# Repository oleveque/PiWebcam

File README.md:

# PiWebcam
* Rémi Armand, *remi.armand@ens-paris-saclay.fr*
* Olivier Lévêque, *olivier.leveque@ens-paris-saclay.fr*

Ce projet, proposé en M2 FeSUP GE à l'École Normale Supérieure Paris-Saclay, a pour objectif de réaliser un système permettant de commander l’orientation d’une webcam à partir d’un serveur web embarqué. Il se base sur l'utilisation d'une *Raspberry Pi 3* et d'un microcontrôleur *AVR-T32U4* (similaire à une *Arduino Leonardo*).

Ce système, nommé *PiWebcam*, vous est présenté en image ci-dessous.

Nous décrirons dans ce manuel son fonctionnement et nous détaillerons son installation et sa configuration.

La chronologie adoptée sera la suivante :
1. Description globale du système ;
2. Configuration du microcontrôleur *AVR-T32U4* ;
3. Installation et configuration de l'ensemble du système Linux sur *Raspberry Pi 3*.

## Description globale du système
Le système PiWebcam répond à la problématique suivante.
> Piloter une webcam à distance en commandant son orientation et son zoom à l’aide d’un serveur embarqué.

La partie matériel, nommé *Cardan 3 axes* et permettant l'orientation de la caméra, est issue d'un projet ultérieur. Seul l'étage d'alimentation a été révisé et une *Raspberry Pi 3* + *PiCamera v2.1* ajoutées. Le diagramme de définition de bloc suivant permet de décomposer le système *PiWebcam* en différents sous-systèmes que nous décrirons dans ce document.

### Cardan 3 axes
Ce sous-système est composé de 2 servomoteurs ([*HS-5565MH*](Ressources/Datasheets/hs5565.pdf)) commandés en position assurant la rotation de la caméra autour de l'axe de roulis et l'axe de tangage, et d'un servomoteur ([*HS-805BB*](Ressources/Datasheets/hs805.pdf)) modifié assurant la rotation de la caméra autour de l'axe de lacet. Ce dernier est commandé en vitesse et permet une rotation totale de la caméra autour de son axe puisque sa butée mécanique a été retirée et son potentiomètre de recopie remplacé par un pont diviseur de tension.

Le schéma suivant décrit sommairement le système.

La liaison électrique entre l'étage supérieur et inférieur est assuré par des contacts glissants, permettant une rotation complète de l'étage supérieur.

L’étage d'alimentation est situé dans la botte du système (étage inférieur) et est assuré par 2 alimentations à découpage (*LM2596* et *MP2307*) délivrant (respectivement) 5V et 7V. Les fichiers *EAGLE* de cet étage sont disponibles dans l'archive du projet.
* Les 5V permettent l’alimentation du servomoteur inférieur assurant la rotation autour de l'axe de lacet ;
* Les 7V permettent l’alimentation des servomoteurs restants, du microcontrôleur, et de la Raspberry. Deux régulateurs linéaires (*L7805CV* et *79ABN05A*) permettent de fournir les 3.3V nécessaire au microcontrôleur et une 3ième alimentation à découpage (*MP2307*) permet de fournir 5V à la Raspberry. Sur cette dernière alimentation, une capacité de 2200uF a été ajoutée en entrée pour diminuer les chutes de tension lors des appels de courant des servomoteurs.

Le schéma suivant illustre la répartion de l'alimentation au sein du système.

La carte de développement utilisé est une *AVR-T32U4* dont l'architecture est inspirée d’une *Arduino Leonardo*. Elle peut être programmée à partir de l’*IDE Arduino*.
Le rôle du microcontrôleur est d'assurer le pilotage des 3 servomoteurs. Les différents pins utilisés de la carte sont présentés sur le schéma suivant.

La communication entre la Raspberry et le microcontrôleur peut être assurée par différents types de liaison (I2C, SPI, UART). La liaison série à travers une connection USB a été retenue pour 2 raisons principales : sa facilité de mise en oeuvre et la possibilité de reprogrammer l'*AVR-T32U4* à partir de la Raspberry.

### Raspberry Pi 3 + PiCamera
La *Raspberry Pi 3* hébergera le serveur à partir duquel l'utilisateur devra se connecter pour piloter le système et visualiser le flux vidéo de la *PiCamera v2.1* (cette caméra a une résolution de 8 mégapixels permettant la mise en oeuvre d'un zoom numérique).

Le serveur diffusera une interface graphique dans lequel le flux vidéo sera streamé. Des boutons permettront de transmettre des ordres au différents servomoteurs via une liaison série entre la Raspberry et le microcontrôleur.

Un screenshot de cette interface vous est présenté ci-dessous.

Afin de mieux visualiser les flux d'informations circulant au sein de la Raspberry, le diagramme de bloc interne ci-dessous illustre les flux principaux.

## Configuration du microcontrôleur *AVR-T32U4*
Pour configurer le microcontrôleur *AVR-T32U4*, il est nécessaire de télécharger l'[IDE Arduino](https://www.arduino.cc/en/Main/Software). Il ne vous restera plus qu'à reprogrammer la carte avec l'un des codes *.ino* disponiblent dans le dossier `Arduino/config` (en choissisant le type de board : *Arduino Leonardo*).
Deux codes vous sont proposés :
* `ArduinoPWM.ino` utilisant la blibliothèque *Servo* d'Arduino pour générer la PWM de commande des servomoteurs ;
* `MyOwnPWM.ino` exploitant les capacités matérielles du microcontrôleur pour générer les PWM. Pour mieux comprendre son fonctionnement, vous pouvez consulter [ce lien](http://r6500.blogspot.ca/2014/12/fast-pwm-on-arduino-leonardo.html) et/ou étudier le code `PWM.ino` dans le dossier `Arduino` qui permet de générer des signaux PWM sur les pins D9, D10, D11 de l'*AVR-T32U4*.

Par défaut, ces codes permettent de commander les servomoteurs via une communication unidirectionnelle série de la Raspberry vers le port `Serial0` du microcontrôleur à la vitesse de *9600 baud*.

Les messages à envoyer sont de simples octets répertoriés dans le tableau ci-dessous.

| Octet | Signification                                   |
| ----- | ----------------------------------------------- |
| `#`   | Retour à la position d'origine                  |
| `@`   | Stopper le mouvement et maintenir la position   |
| `U`   | Rotation autour de l'axe de tangage dans le sens positif |
| `D`   | Rotation autour de l'axe de tangage dans le sens négatif |
| `R`   | Rotation autour de l'axe de lacet dans le sens positif   |
| `L`   | Rotation autour de l'axe de lacet dans le sens positif   |
| `W`   | Rotation autour de l'axe de roulis dans le sens positif  |
| `V`   | Rotation autour de l'axe de roulis dans le sens négatif  |

Il est possible d'envoyer un ordre similtanément aux 3 servomoteurs en transmettant l'octet `#` suivit respectivement des positions angulaires des servomoteurs associé au roulis, au tangage et la vitesse angulaire du servomoteur associé au lacet, en séparant les données par un caractère quelconque : par exemple `#350/-260/40`.

## Installation et configuration de l'ensemble du système Linux sur *Raspberry Pi 3*
1. Installation de Raspbian ;
2. Configuration du point d’accès Wifi ;
3. Configuration du streaming vidéo pour une *PiCamera* ;
4. Installation du serveur *nweb* modifié ;
5. Configuration de la communication série entre l'Arduino et Linux TTY ;
6. Configuration du lancement automatique des différents processus au démarrage du système.

Une fois configuré, l'interface de pilotage est accéssible à l'adresse `192.168.3.1:8081` sous réserve d'être connecté au réseau Wifi `PiWebcam` (mot de passe : `mdppiwebcam`) généré par le système.

### Installation de Raspbian
Pour télécharger l'image, rendez-vous sur la [page officiel](https://www.raspberrypi.org/downloads/raspbian/).
Suivez le [guide d'installation](https://www.raspberrypi.org/documentation/installation/installing-images/) si vous ne savez pas (ou plus) comment installer cette image sur une carte SD.

### Configuration du point d’accès Wifi
La configuration du point d'accès Wifi est inspiré de [ce tutoriel](https://www.g33k-zone.org/post/2016/05/11/Configurer-le-Raspberry-Pi-en-point-d-acc%C3%A8s-Wifi).

Cette configuration est valable pour une *Raspberry Pi 3* disposant d'un module Wifi intégré. Il est cependant possible d'effectuer une configuration similaire sur un autre modèle à l'aide d'un dongle Wifi.

**Remarque :** Pour effectuer cette configuration, il est nécessaire d'être directement connecté à la Raspberry avec un moniteur, un clavier + souris, et une connection internet.

Commencez par installer les packages *dnsmasq* et *hostapd*.
```
sudo apt-get install dnsmasq hostapd
```

La première étape consiste à forcer l'adresse IP pour le point d'accès. Par défaut, le wifi de Raspberry étant en *dhcp*, nous allons devoir éditer `/etc/dhcpcd.conf` pour forcer une adresse IP statique (`192.168.3.1` dans notre cas), en ajoutant les lignes suivantes :
```
interface wlan0  
   static ip_address=192.168.3.1/24
```

Ensuite, nous allons bloquer la négociation automatique de bail dans le fichier `/etc/network/interfaces`.
Il faut rechercher le bloc suivant :
```
allow-hotplug wlan0  
iface wlan0 inet manual  
 #   wpa-conf /etc/wpa_supplicant/wpa_supplicant.conf
```

 Il suffit de commenter la ligne d'appel à `wpa_supplicant.conf` (en ajoutant le `#`).

Nous pouvons maintenant redémarrer le wifi à l'aide de la commande suivante.
```
sudo service dhcpcd restart
```

*hostapd* est le logiciel qui permet de gérer le point d'accès, il est donc le coeur de notre système. Sa configuration se fait dans le fichier `/etc/hostapd/hostapd.conf` qu'il faut créer :

```
cd /etc/hostapd/
sudo touch hostapd.conf
sudo nano hostapd.conf
```

Et le remplir avec :
```
# Nom de l'interface wifi (celle par défaut)
interface=wlan0
# Utilisation du driver nl80211,
driver=nl80211
# Nom du réseau wifi (SSID)
ssid=PiWebcam
# Mode du wifi (bande 2.4GHz)
hw_mode=g
# Canal 6
channel=6
# Activer le 802.11n
ieee80211n=1
# Activer le WMM
wmm_enabled=1
# Activer les canaux 40MHz avec 20ns d'intervalle
ht_capab=[HT40][SHORT-GI-20][DSSS_CCK-40]
# Accepter toutes les adresses MAC (pas de restriction d'appareil)
macaddr_acl=0
# Utiliser l'authentification WPA
auth_algs=1
# Ne pas diffuser le SSID
ignore_broadcast_ssid=0
# Utiliser WPA2
wpa=2
# Utiliser une clé partagée
wpa_key_mgmt=WPA-PSK
# Mot de passe du réseau
wpa_passphrase=mdppiwebcam
# Utilisation d'AES plutôt que de TKIP
rsn_pairwise=CCMP
```

Nous pouvons alors à présent tester le fonctionnement du point d'accès.
```
sudo /usr/sbin/hostapd  /etc/hostapd/hostapd.conf
```
Cette commande lance le point d'accès et permet d'avoir le log d'activité directement dans la console. Avec un équipement wifi (gsm, tablette, portable, ...), essayez de vous connecter au réseau `PiWebcam`, normalement la tentative de connexion apparaît.

Une fois que le point d'accès fonctionne, coupez le (*Ctrl+C*) et placez le en démarrage automatique, en éditant le fichier `/etc/default/hostapd`.
```
#DAEMON_CONF=""         =>           DAEMON_CONF="/etc/hostapd/hostapd.conf"
```

*dnsmasq* est un petit serveur DNS qui intègre un serveur *DHCP*. Il permettra d'attribuer les adresses IP aux clients qui se connecteront sur le point d'accès.
Sauvegardez son fichier de configuration initial (`/etc/dnsmasq.conf`, qui n'est pas entierement commenté!) puis créez en une nouvelle version :
```
# Interface à utiliser
interface=wlan0
# Limiter le fonctionnement à l'interface déclarée
bind-interfaces
# Transférer les requêtes DNS sur les DNS d'OpenDns
server=208.67.222.222
# Ne pas forwarder les requêtes "locales" (sans nom de domaine)
domain-needed
# Fausse résolution inverse pour les réseaux privés. Toutes les requêtes DNS inverses pour des adresses IP privées (ie 192.168.x.x, etc…) qui ne sont pas trouvées dans /etc/hosts ou dans le fichier de baux DHCP se voient retournées une réponse “pas de tel domaine” (”no such domain”) au lieu d’être transmises
bogus-priv
# Plage DHCP : on attribuera les adresses IP entre 192.168.3.50 et 192.168.3.150 pour une durée de 12h
dhcp-range=192.168.3.50,192.168.3.150,12h
```

Vous avez actuellement un point d'accès fonctionnel mais limité au réseau local. La suite de ce tutoriel est facultative si vous ne souhaitez pas d'accès à internet via votre Raspberry.

Nous allons utiliser *iptables* pour ajouter des règles de routage.

Il faut commencer par modifier les règles de sécurité dans `/etc/sysctl.conf` pour autoriser le transfert IPv4 (ou IP forwarding) en décommantant la ligne suivante.
```
net.ipv4.ip_forward=1
```

Cette modification ne sera prise en compte qu'au prochain redémarrage de votre Raspberry, mais il est possible de forcer son activation immédiate à l'aide de la commande suivante.
```
sudo sh -c "echo 1 > /proc/sys/net/ipv4/ip_forward"
```

Maintenant que le transfert IPv4 est autorisé, nous allons créer les règles qui vont transférer les requêtes Wifi vers le port ethernet en excécutant les commandes suivantes.
```
sudo iptables -t nat -A POSTROUTING -o eth0 -j MASQUERADE  
sudo iptables -A FORWARD -i eth0 -o wlan0 -m state --state RELATED,ESTABLISHED -j ACCEPT  
sudo iptables -A FORWARD -i wlan0 -o eth0 -j ACCEPT
```

Pour que ces règles soient appliquées à chaque démarrage, nous allons commencer par les sauvegarder dans un fichier `/etc/iptables.ipv4.nat`.
```
sudo sh -c "iptables-save > /etc/iptables.ipv4.nat"
```

Ensuite, nous allons créer un fichier qui sera appelé automatiquement au démarrage du serveur *dhcp*
```
sudo echo "iptables-restore < /etc/iptables.ipv4.nat" > /lib/dhcpcd/dhcpcd-hooks/70-ipv4-nat
```

Pour pouvoir tester votre système sans avoir à le rebooter, il suffit de lancer les daemons manuellement.
```
sudo service hostapd start  
sudo service dnsmasq start
```

Vous disposez à présent dans point d'accés Wifi via la Raspberry.

### Configuration du streaming vidéo pour une *PiCamera*
Pour le streaming vidéo, nous utilisons le package *mjpg-streamer*. Pour plus d'informations, suivez [ce lien](https://doc.ubuntu-fr.org/mjpg-streamer).

Avant de commencer, assurez vous que le package *subversion* est bien installé.
```
sudo apt-get install subversion
```

L'installation de *mjpg-streamer* peut alors commencer.
```
sudo apt-get install libjpeg62-dev
sudo apt-get install libjpeg-dev
svn checkout svn://svn.code.sf.net/p/mjpg-streamer/code/  /mjpg-streamer
cd /mjpg-streamer/mjpg-streamer
sudo make
sudo make install
```

Pour pouvoir lancer le streaming vidéo, il faut charger le module `bcm2835-v4l2` à l'aide de la commande suivante à chaque démarrage de la Raspberry. La camera doit être branché au démarrage. Pour plus d'informations, consultez [ce lien](http://www.epingle.info/?p=3224).
```
sudo modprobe bcm2835-v4l2
```

Pour éviter d’avoir à exécuter cette commande à chaque démarrage, il suffit d’ajouter le module `bcm2835-v4l2` à l’ensemble des modules lancés par Linux au démarrage en ajoutant le nom du module à la fin du fichier  `/etc/modules`.

Le streaming vidéo se lance à l'aide de la commande suivante.
```
mjpg_streamer -i "/usr/local/lib/input_uvc.so -d /dev/video0 -f 24 -r 320x180" -o "/usr/local/lib/output_http.so -n -w /usr/local/www -p 8001"
```
La vérification de l'existence de `/dev/video0` permet de savoir sur le module s’est bien lancer au démarrage.

Le flux vidéo de la *PiCamera* devrait à présent être accessible à l'adresse `192.168.3.1:8001`.

### Installation du serveur *nweb* modifié
La serveur web mis en oeuvre repose sur le serveur *nweb* proposé par [Ankush Agarwal](https://github.com/ankushagarwal/nweb). Nous l'avons légèrement modifié pour qu'il prennent en compte la gestion de *cgi*.

Pour l'installer, placez le fichier `nweb23.c` et le dossier `serveur` contenant le site dans un répertoire sensible (et non pas dans un répertoire système comme `/` ou `/temp`). Par exemple dans `/home`. Puis rendez le dossier lisible.
```
chmod ugo+r /home/serveur
```
Compilez ensuite le serveur *nweb* et rendez le executable.
```
cc /home/nweb23.c -o /home/nweb
chmod 777 /home/nweb
```
Décidez ensuite du numéro du port que vous utiliserez (ici *8081*). Puis lancez *nweb* à l'aide de la commande suivante.
```
/home/nweb 8081 /home/serveur
```

Voilà, le serveur *nweb* fonctionne à présent et l'interface de pilotage du système *PiWebcam* est disponile à l'adresse `192.168.3.1:8081`

### Configuration de la communication série entre l'Arduino et Linux TTY
Pour configurer la connection Série entre la Raspberry et le microcontrôleur avec la bonne parité, vitesse... excécutez la commande suivante. Pour plus d'information, consultez [ce lien](http://playground.arduino.cc/Interfacing/LinuxTTY).
```
stty -F /dev/ttyACM0 cs8 9600 ignbrk -brkint -icrnl -imaxbel -opost -onlcr -isig -icanon -iexten -echo -echoe -echok -echoctl -echoke noflsh -ixon -crtscts
```

Pour envoyer un message de type *String* au microcontrôleur, nous utiliserons les commandes :
```
#avec fin de ligne
echo "Hello Arduino" > /dev/ttyUSB0

#sans fin de ligne
echo -n "Hello" > /dev/ttyUSB0
```

Pour lire un message de type String envoyé du microcontrôleur, nous utiliserons la commande :
```
tail -f /dev/ttyUSB0
```

### Lancement des différents processus au démarrage de la Raspberry
Le lancement du serveur *nweb* et du streaming vidéo au démarrage de la Raspberry se fait à l'aide du fichier `lancementServeur.sh`. (Nous supposerons que ce fichier disponible dans l'archive du projet et se trouve dans `/home`).

Déplacez le script shell dans le répertoire `/etc/init.d` qui contient les différents scripts lancés au démarrage, et rendait le executable via les commandes suivantes.

```
sudo mv /home/lancementServeur.sh /etc/init.d/lancementServeur
sudo chmod 777 /etc/init.d/lancementServeur
```

Les liens symboliques associés au fichier `lancementServeur` pour son démarrage et son arrêt au lancement et à l'arrêt de la Raspberry sont générés à l'aide de la commande suivante.
```
sudo update-rc.d lancementServeur defaults
```
Le lien symbolique créé dans `rc3.d` est `S02lancementserveur`. Nous pouvons renommer le lien en `S99lancementserveur` pour qu'il se lance en dernier.

À présent le système *PiCamera* est entièrement installé et configuré.

Enjoy & have a lot of fun...

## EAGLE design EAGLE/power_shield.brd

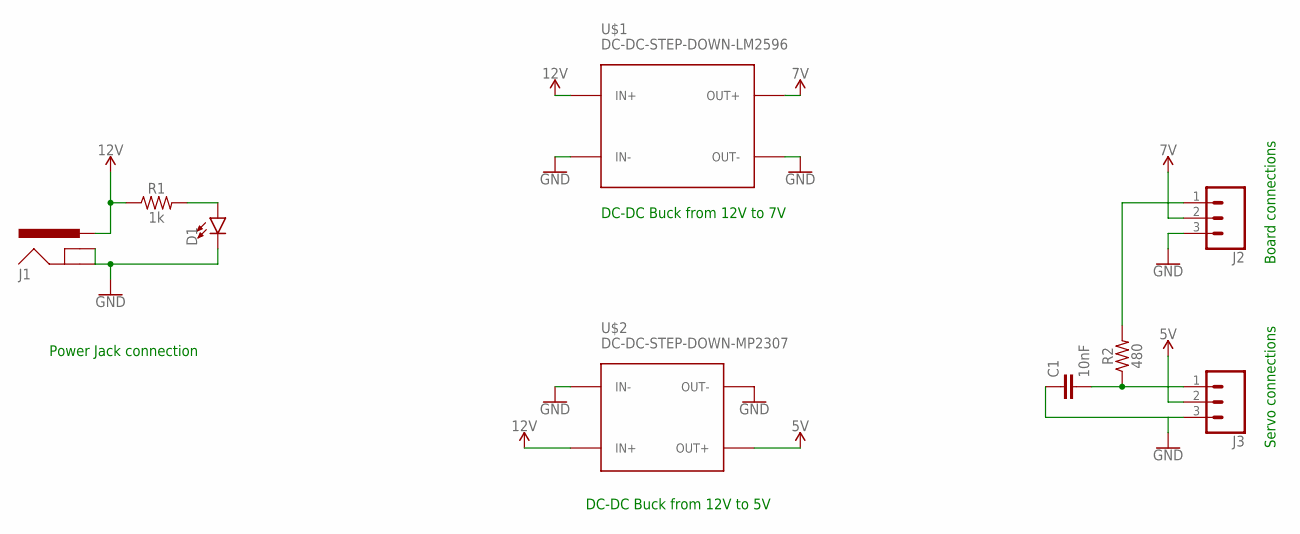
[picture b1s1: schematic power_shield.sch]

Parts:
C1: 10nF; 1206
D1: LED5MM; LED_5MM
J1: POWER_JACKPTH_LOCK; POWER_JACK_PTH_LOCK
J2, J3: CONN_03; 1X03
R1: 1k; 1206
R2: 480; 1206
U$1: DC-DC-STEP-DOWN-LM2596
U$2: DC-DC-STEP-DOWN-MP2307

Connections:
5V: J3.2, U$2.OUT+
12V: J1.PWR, R1.1, U$1.IN+, U$2.IN+
GND: C1.1, D1.K (C), J1.GND, J1.GNDBREAK, J2.3, J3.3, U$1.IN-, U$1.OUT-, U$2.IN-, U$2.OUT-
unnamed: D1.A, R1.2
unnamed: C1.2, J3.1, R2.1
unnamed: J2.1, R2.2
VCC: J2.2, U$1.OUT+

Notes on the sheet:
Board connections
Servo connections
DC-DC Buck from 12V to 5V
DC-DC Buck from 12V to 7V
Power Jack connection

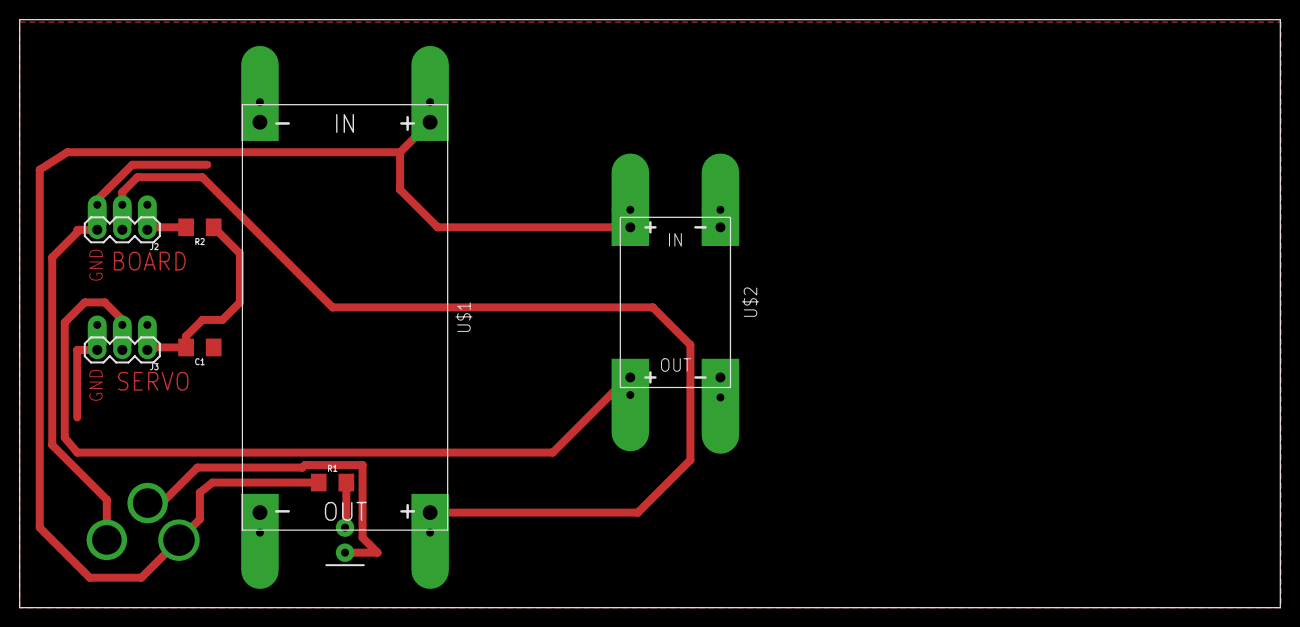
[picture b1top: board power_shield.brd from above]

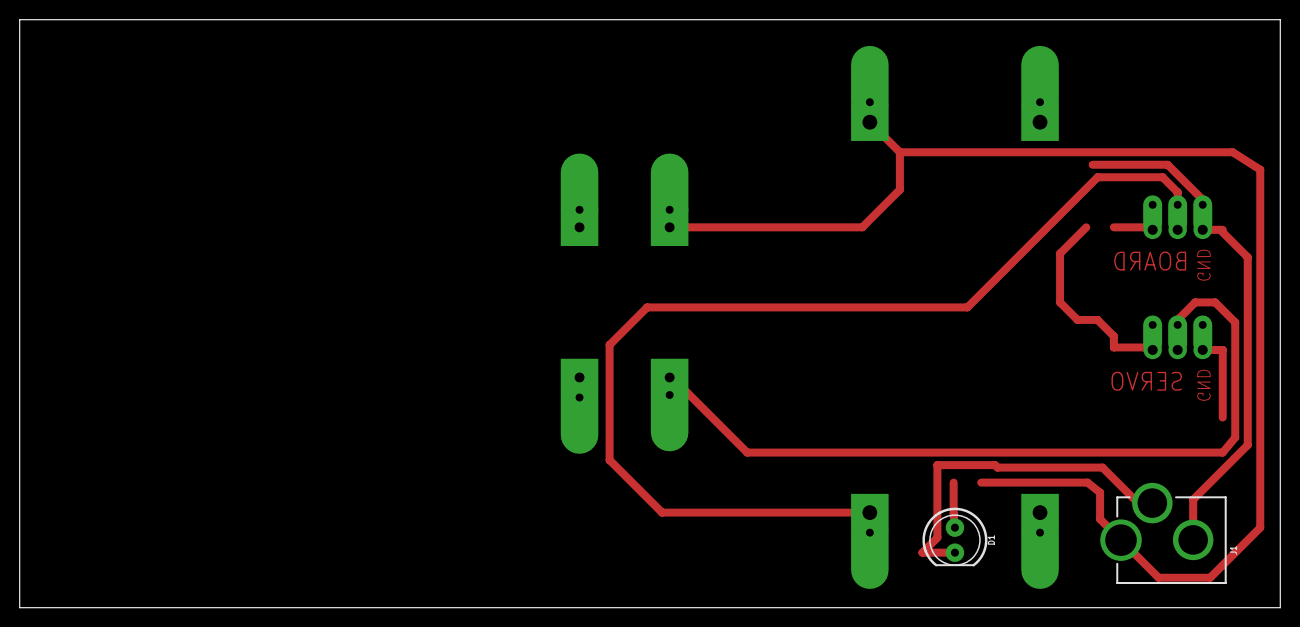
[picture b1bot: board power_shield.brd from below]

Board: 2 copper layers, 127.9 x 59.7 mm, 9 parts (2 on the bottom side), 7 nets.

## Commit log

2017-04-24 add project
2017-05-02 Reorganize files
2017-05-02 add documentation
2017-05-02 fix bug
2017-05-02 add contact information
2017-05-02 Update picture
2017-05-04 add TP
2017-05-09 add pictures
2017-05-09 update TP
2017-05-12 Update pin Lacet
2017-05-14 add comments PWM.ino
2017-05-15 last update
2017-05-15 fix issues
2017-05-17 corrections

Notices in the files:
parts and their libraries:
SparkFun-LED: Licensing: Creative Commons ShareAlike 4.0 International - https://creativecommons.org/licenses/by-sa/4.0
diy-modules_modified: Released under the Creative Commons Attribution 4.0 International License: http://creativecommons.org/licenses/by/4.0
